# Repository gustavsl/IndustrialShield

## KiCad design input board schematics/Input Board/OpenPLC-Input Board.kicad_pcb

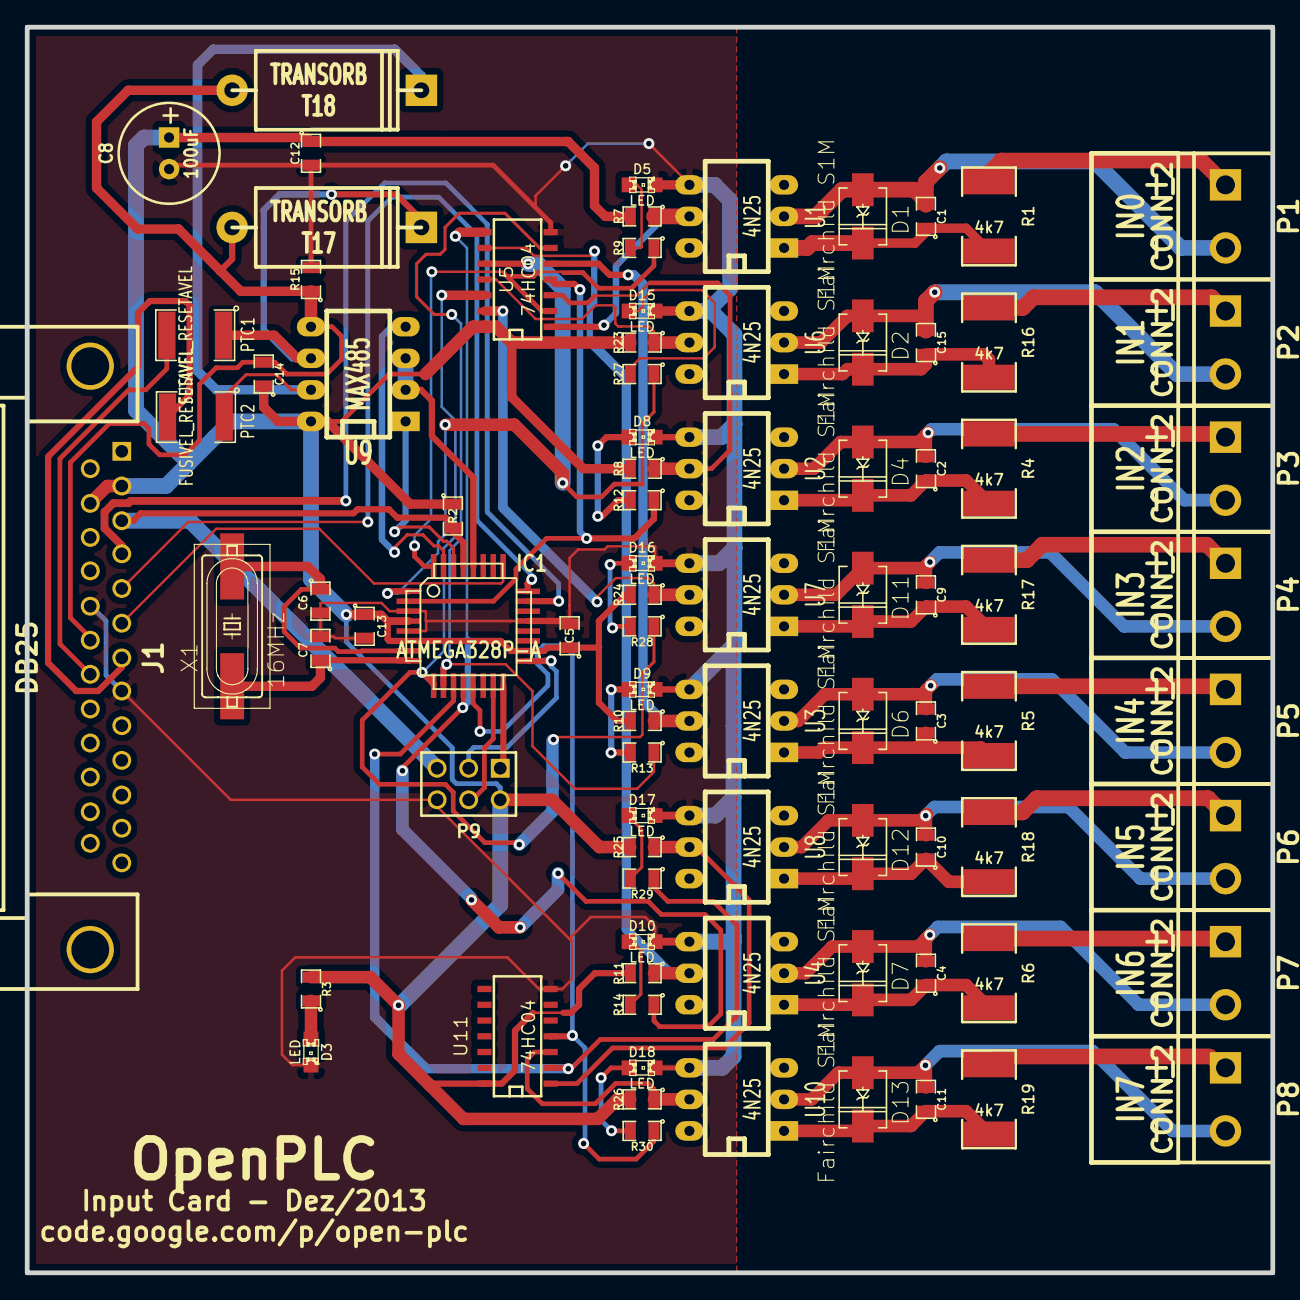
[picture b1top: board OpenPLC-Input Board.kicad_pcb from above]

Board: 2 copper layers, 100.3 x 100.3 mm, 86 parts (0 on the bottom side), 68 nets.

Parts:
C1, C2, C3, C4, C5, C9, C10, C11, C12, C13, C14, C15: 100nF; SM0805
C6, C7: 22pF; SM0805
C8: 100uF; C1V8
D1, D2, D4, D6, D7, D11, D12, D13: Fairchild S1M; DO214_OPLC
D3, D5, D8, D9, D10, D15, D16, D17, D18: LED; LED-0805
IC1: ATMEGA328P-A; TQFP32
J1: DB25; DB25MC
P1, P2, P3, P4, P5, P6, P7, P8: CONN_2; bornier2
P9: ICSP - 3X2; pin_array_3x2
PTC1, PTC2: FUSIVEL_RESETAVEL; SM1812
R1, R4, R5, R6, R16, R17, R18, R19: 4k7; SM2512
R2, R7, R8, R10, R11, R23, R24, R25, R26: 10k; SM0805
R3, R9, R12, R13, R14, R27, R28, R29, R30: 1k; SM0805
R15: 0R; SM0805
T17, T18: TRANSORB; D6
U1, U2, U3, U4, U6, U7, U8, U10: 4N25; DIP-6__300_ELL
U5, U11: 74HC04; SO14E
U9: MAX485; DIP-8__300_ELL
X1: 16MHz; crystal-HC49UP

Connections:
+5V: C5.1, C8.1, C12.1, C13.1, C14.1, IC1.4, IC1.6, IC1.18, J1.2, J1.15, P9.2, R2.1, R3.2, R7.2, R8.2, R10.2, R11.2, R23.2, R24.2, R25.2, R26.2, U5.14, U9.8, U11.14
/A: J1.20, PTC1.2
/B: J1.7, PTC2.2
/CPU_RESET: IC1.29, J1.3, P9.5, R2.2
/D0: IC1.23, J1.4
/D1: IC1.24, J1.5
/D2: IC1.25, J1.6
/E1+: P1.1, R1.1
/E1-: C1.2, D1.1, P1.2, U1.2
/E2+: P2.1, R16.1
/E2-: C15.2, D2.1, P2.2, U6.2
/E3+: P3.1, R4.1
/E3-: C2.2, D4.1, P3.2, U2.2
/E4+: P4.1, R17.1
/E4-: C9.2, D11.1, P4.2, U7.2
/E5+: P5.1, R5.1
/E5-: C3.2, D6.1, P5.2, U3.2
/E6+: P6.1, R18.1
/E6-: C10.2, D12.1, P6.2, U8.2
/E7+: P7.1, R6.1
/E7-: C4.2, D7.1, P7.2, U4.2
/E8+: P8.1, R19.1
/E8-: C11.2, D13.1, P8.2, U10.2
/EN: IC1.28, U9.2, U9.3
/GND_485: C14.2, J1.19, R15.1, T17.1, T18.1, U9.5
/MISO: IC1.16, P9.1
/MOSI: IC1.15, P9.4
/RX: IC1.30, U9.1
/SCK: IC1.17, P9.3
/TX: IC1.31, U9.4
/X0: IC1.32, R9.1, U5.2
/X1: IC1.1, R27.1, U5.10
/X2: IC1.2, R12.1, U5.4
/X3: IC1.9, R28.1, U5.12
/X4: IC1.10, R13.1, U5.6
/X5: IC1.11, R29.1, U11.2
/X6: IC1.12, R14.1, U5.8
/X7: IC1.13, R30.1, U11.4
GND: C5.2, C6.2, C7.2, C8.2, C12.2, C13.2, D3.2, D5.2, D8.2, D9.2, D10.2, D15.2, D16.2, D17.2, D18.2, IC1.3, IC1.5, IC1.21, J1.8, J1.18, P9.6, R15.2, U1.4, U2.4, U3.4, U4.4, U5.7, U6.4, U7.4, U8.4, U10.4, U11.7
unnamed: D3.1, R3.1
unnamed: D17.1, R29.2
unnamed: D9.1, R13.2
unnamed: R10.1, U3.5, U5.5
unnamed: C9.1, D11.2, R17.2, U7.1
unnamed: C2.1, D4.2, R4.2, U2.1
unnamed: C15.1, D2.2, R16.2, U6.1
unnamed: C6.1, IC1.7, X1.2
unnamed: C1.1, D1.2, R1.2, U1.1
unnamed: D5.1, R9.2
unnamed: R23.1, U5.11, U6.5
unnamed: R7.1, U1.5, U5.1
unnamed: C7.1, IC1.8, X1.1
unnamed: D15.1, R27.2
unnamed: PTC2.1, T18.2, U9.7
unnamed: D10.1, R14.2
unnamed: D18.1, R30.2
unnamed: D16.1, R28.2
unnamed: D8.1, R12.2
unnamed: R8.1, U2.5, U5.3
unnamed: R24.1, U5.13, U7.5
unnamed: R26.1, U10.5, U11.3
unnamed: R11.1, U4.5, U5.9
unnamed: R25.1, U8.5, U11.1
unnamed: PTC1.1, T17.2, U9.6
unnamed: C4.1, D7.2, R6.2, U4.1
unnamed: C3.1, D6.2, R5.2, U3.1
unnamed: C11.1, D13.2, R19.2, U10.1
unnamed: C10.1, D12.2, R18.2, U8.1

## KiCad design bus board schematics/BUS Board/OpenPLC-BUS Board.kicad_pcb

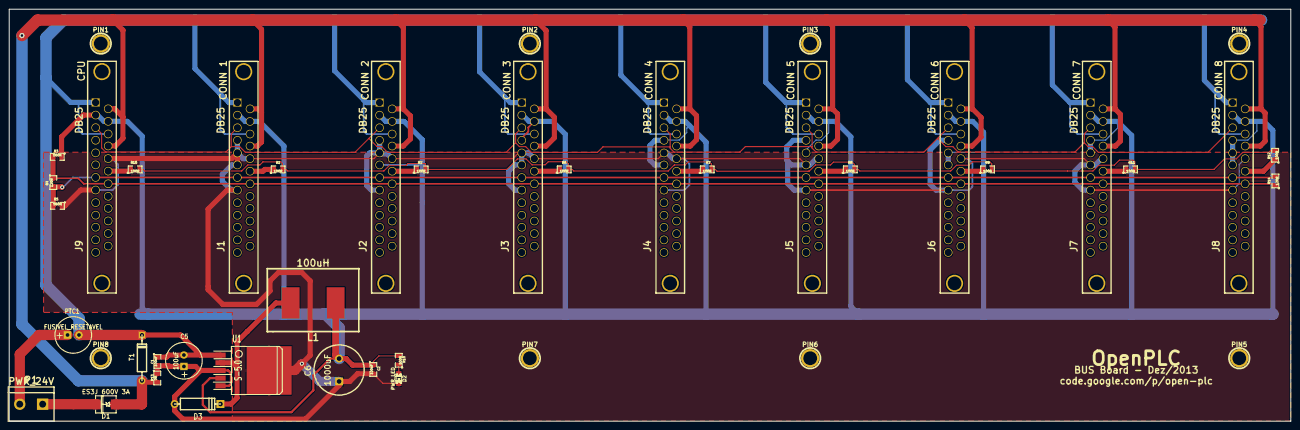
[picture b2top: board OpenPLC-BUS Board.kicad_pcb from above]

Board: 2 copper layers, 284.5 x 91.4 mm, 44 parts (0 on the bottom side), 21 nets.

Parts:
C1, C2: 100nF; SM0805
C5: 100uF; C1V8
C6: 1000uF; C2V10
D1: ES3J 600V 3A; DO-214AA(SMB)
D2: PWR_LED; LED-0805
D3: 1N5822; D4
J1, J2, J3, J4, J5, J6, J7, J8, J9: DB25; DB25_Large
L1: 100uH; bourns-srr1206
P1: PWR_24V; bornier2
PIN1: P1; 1pin
PIN2: P2; 1pin
PIN3: P3; 1pin
PIN4: P4; 1pin
PIN5: P5; 1pin
PIN6: P6; 1pin
PIN7: P7; 1pin
PIN8: P8; 1pin
PTC1: FUSIVEL_RESETAVEL; C1V8
R1, R2, R6, R7, R8, R9, R11, R12, R15: 100R; SM0805
R3, R5: 560R; SM0805
R4, R14: 120R; SM0805
R10: 500R; SM0805
R13: 0R; SM0805
T1: TRANSORB; DO-41
U1: S-5.0; TO263-5

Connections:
+5V: C2.1, C6.2, J1.2, J1.15, J2.2, J2.6, J2.15, J3.2, J3.4, J3.15, J4.2, J4.4, J4.6, J4.15, J5.2, J5.5, J5.15, J6.2, J6.5, J6.6, J6.15, J7.2, J7.4, J7.5, J7.15, J8.2, J8.4, J8.5, J8.6, J8.15, J9.2, J9.15, L1.2, R3.1, R10.2, U1.4
/24V: C1.1, C5.2, J1.1, J1.16, J2.1, J2.16, J3.1, J3.16, J4.1, J4.16, J5.1, J5.16, J6.1, J6.16, J7.1, J7.16, J8.1, J8.16, J9.1, J9.16, PTC1.2, T1.2, U1.1
/485_A: J1.20, J2.20, J3.20, J4.20, J5.20, J6.20, J7.20, J8.20, J9.20, R3.2, R4.1, R14.1
/485_B: J1.7, J2.7, J3.7, J4.7, J5.7, J6.7, J7.7, J8.7, J9.7, R4.2, R5.2, R14.2
/CPU_RESET: J1.3, J2.3, J3.3, J4.3, J5.3, J6.3, J7.3, J8.3, J9.3
/GND_24: D1.1, J1.14, J1.17, J2.14, J2.17, J3.14, J3.17, J4.14, J4.17, J5.14, J5.17, J6.14, J6.17, J7.14, J7.17, J8.14, J8.17, J9.14, J9.17, R13.2, T1.1
/GND_485: R1.2, R2.2, R6.2, R7.2, R8.2, R9.2, R11.2, R12.2, R15.2
GND: C1.2, C2.2, C5.1, C6.1, D2.2, D3.1, J1.4, J1.5, J1.6, J1.8, J1.18, J2.4, J2.5, J2.8, J2.18, J3.5, J3.6, J3.8, J3.18, J4.5, J4.8, J4.18, J5.4, J5.6, J5.8, J5.18, J6.4, J6.8, J6.18, J7.6, J7.8, J7.18, J8.8, J8.18, J9.8, J9.18, R5.1, R13.1, U1.3, U1.5
unnamed: J2.19, R2.1
unnamed: J6.19, R9.1
unnamed: J8.19, R12.1
unnamed: J4.19, R7.1
unnamed: J7.19, R11.1
unnamed: J9.19, R15.1
unnamed: D3.2, L1.1, U1.2
unnamed: P1.2, PTC1.1
unnamed: D1.2, P1.1
unnamed: D2.1, R10.1
unnamed: J5.19, R8.1
unnamed: J1.19, R1.1
unnamed: J3.19, R6.1

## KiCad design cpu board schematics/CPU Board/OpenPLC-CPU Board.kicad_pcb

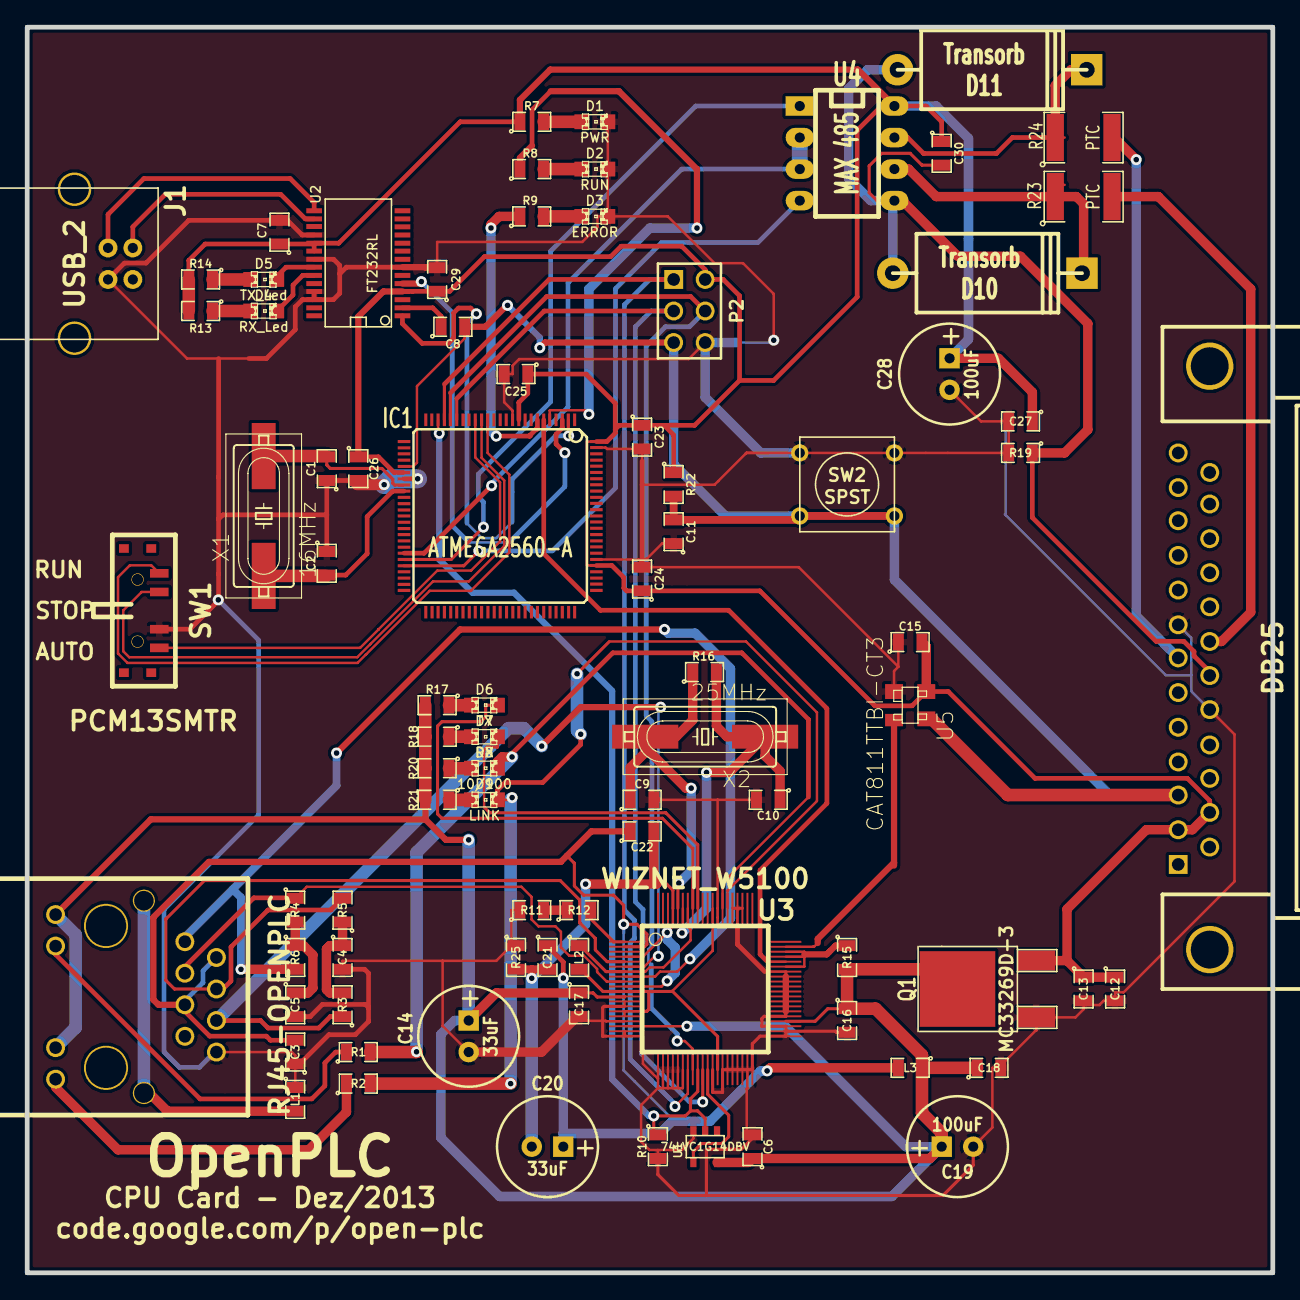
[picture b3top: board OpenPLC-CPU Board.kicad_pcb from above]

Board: 2 copper layers, 100.3 x 100.3 mm, 84 parts (0 on the bottom side), 64 nets.

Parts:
C1, C2, C9, C10: 22pF; SM0805
C3, C4, C5, C6, C7, C8, C11, C12, C15, C16, C17, C18, C21, C22, C23, C24, C25, C26, C27, C29, C30: 100nF; SM0805
C13: 47uF; SM0805
C14, C20: 33uF; C1V8
C19, C28: 100uF; C1V8
D1: PWR; LED-0805
D2: RUN; LED-0805
D3: ERROR; LED-0805
D4: RX_Led; LED-0805
D5: TX_Led; LED-0805
D6: TX; LED-0805
D7: RX; LED-0805
D8: 10/100; LED-0805
D9: LINK; LED-0805
D10, D11: Transorb; D6
IC1: ATMEGA2560-A; TQFP_100
J1: USB_2; USB_B
J2: DB25; DB25MC
L1: BLM21PG300 - 250mA 1uH; SM0805
L2, L3: BLM21PG300; SM0805
P1: RJ45-OPENPLC; RJ45_SI60062
P2: ICSP; pin_array_3x2
Q1: MC33269D-3; DPAK2
R1, R2: 1K; SM0805
R3, R4, R5, R6: 49R9; SM0805
R7, R8, R9, R17, R18, R20, R21: 1k; SM0805
R10, R15, R22: 10k; SM0805
R11: 300R; SM0805
R12: 12k; SM0805
R13, R14: 500R; SM0805
R16: 1M; SM0805
R19, R25: 0R; SM0805
R23, R24: PTC; SM1812
SW1: PCM13SMTR
SW2: SPST; SW_PUSH_SMALL
U1: 74LVC1G14DBV; SOT23-5
U2: FT232RL; SSOP28
U3: WIZNET_W5100; wiznet_w5100
U4: MAX 485; DIP-8__300_ELL
U5: CAT811TTBI-CT3; -SOT143-W
X1: 16MHz; crystal-HC49UP
X2: 25MHz; crystal-HC49UP

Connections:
+3.3V: C6.1, C14.1, C16.1, C17.1, C18.1, C19.1, L3.1, P1.11, P1.13, Q1.2, R15.2, R17.2, R18.2, R20.2, R21.2, U1.5, U3.12, U3.18, U3.44
+5V: C7.1, C12.1, C13.1, C15.2, C23.1, C24.1, C25.1, C26.1, C27.1, C28.1, C29.1, C30.1, IC1.10, IC1.31, IC1.80, IC1.100, J2.2, J2.15, P2.2, Q1.3, R7.1, R13.2, R14.2, R22.1, U2.4, U2.19, U2.20, U4.8, U5.4
/3V3A: C3.2, C20.1, C21.1, C22.1, L3.2, P1.2, P1.5, U3.2
/485_A: J2.20, R23.2
/485_B: J2.7, R24.2
/485_RX: IC1.45, U4.1
/485_TX: IC1.46, U4.4
/CPU_ERROR: IC1.7, R9.1
/CPU_RESET: C8.2, C11.2, IC1.30, J2.3, P2.5, R22.2, SW2.2, U5.3
/CPU_RUN: IC1.5, R8.1
/GND_485: C30.2, D10.1, D11.1, J2.19, R19.1, U4.5
/INT: IC1.6, U3.56
/LINKLED: D9.2, R2.2, U3.66
/MISO: IC1.22, P2.1, U3.27
/MOSI: IC1.21, P2.4, U3.28
/RESET_W: U3.59, U5.2
/RXIN: P1.6, R3.1, U3.6
/RXIP: P1.4, R5.2, U3.5
/SCK: IC1.20, P2.3, U3.30
/SPDLED: D8.2, R1.2, U3.67
/SS: IC1.23, R10.1, U1.2, U3.29
/TXON: P1.3, R4.1, U3.9
/TXOP: P1.1, R6.2, U3.8
/TX_EN: IC1.44, U4.2, U4.3
/USB_RX: IC1.2, U2.1
/USB_TX: IC1.3, U2.5
GND: C1.1, C2.1, C3.1, C4.2, C5.2, C6.2, C7.2, C9.2, C10.2, C11.1, C12.2, C13.2, C14.2, C15.1, C16.2, C17.2, C18.2, C19.2, C23.2, C24.2, C25.2, C26.2, C27.2, C28.2, C29.2, D1.2, D2.2, D3.2, IC1.11, IC1.32, IC1.81, IC1.99, J1.4, J2.8, J2.18, L1.1, P1.8, P2.6, Q1.1, R10.2, R11.1, R19.2, R25.1, SW1.3, SW2.1, U1.3, U2.7, U2.18, U2.21, U2.25, U2.26, U3.13, U3.14, U3.17, U3.19, U3.20, U3.21, U3.22, U3.23, U3.24, U3.25, U3.26, U3.32, U3.34, U3.35, U3.36, U3.37, U3.38, U3.39, U3.40, U3.41, U3.42, U3.43, U3.45, U3.46, U3.47, U3.48, U3.49, U3.50, U3.51, U3.52, U3.53, U3.54, U3.63, U3.64, U3.65, U3.68, U5.1
GNDA: C20.2, C21.2, C22.2, R25.2, U3.4, U3.10, U3.77
unnamed: L2.1, U3.7, U3.74
unnamed: R15.1, U3.55, U3.57, U3.58
unnamed: R12.2, U3.1
unnamed: D6.1, R17.1
unnamed: D7.2, U3.72
unnamed: D7.1, R18.1
unnamed: D6.2, U3.73
unnamed: C10.1, R16.2, U3.75, X2.1
unnamed: D8.1, R20.1
unnamed: D9.1, R21.1
unnamed: R11.2, R12.1
unnamed: C5.1, R4.2, R6.1
unnamed: P1.12, R1.1
unnamed: L1.2, P1.9, P1.10
unnamed: P1.14, R2.1
unnamed: C1.2, IC1.33, X1.2
unnamed: D4.2, U2.23
unnamed: C2.2, IC1.34, X1.1
unnamed: C8.1, U2.2
unnamed: D4.1, R13.1
unnamed: D5.1, R14.1
unnamed: J1.3, U2.15
unnamed: J1.2, U2.16
unnamed: D10.2, R23.1, U4.6
unnamed: D11.2, R24.1, U4.7
unnamed: D2.1, R8.2
unnamed: D3.1, R9.2
unnamed: D1.1, R7.2
unnamed: C9.1, R16.1, U3.76, X2.2
unnamed: L2.2, U3.11, U3.15, U3.16, U3.33, U3.69
unnamed: C4.1, R3.2, R5.1
unnamed: IC1.15, SW1.1
unnamed: IC1.17, SW1.4
unnamed: IC1.16, SW1.2
unnamed: D5.2, U2.22
unnamed: U1.4, U3.31

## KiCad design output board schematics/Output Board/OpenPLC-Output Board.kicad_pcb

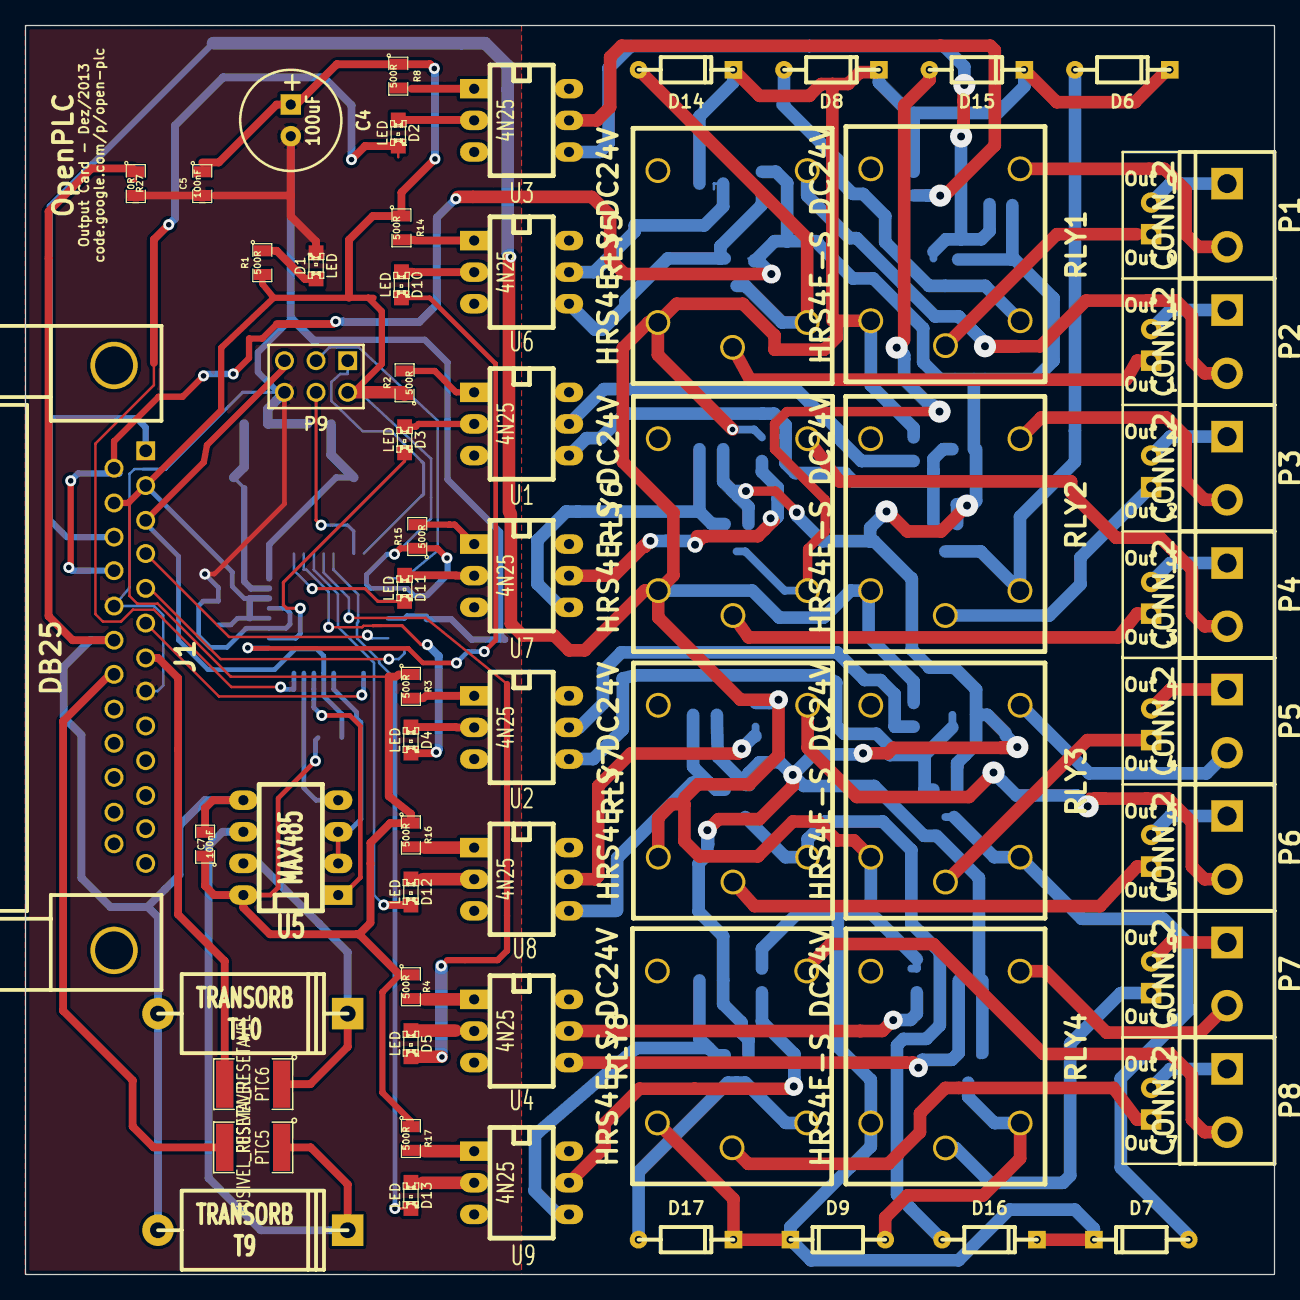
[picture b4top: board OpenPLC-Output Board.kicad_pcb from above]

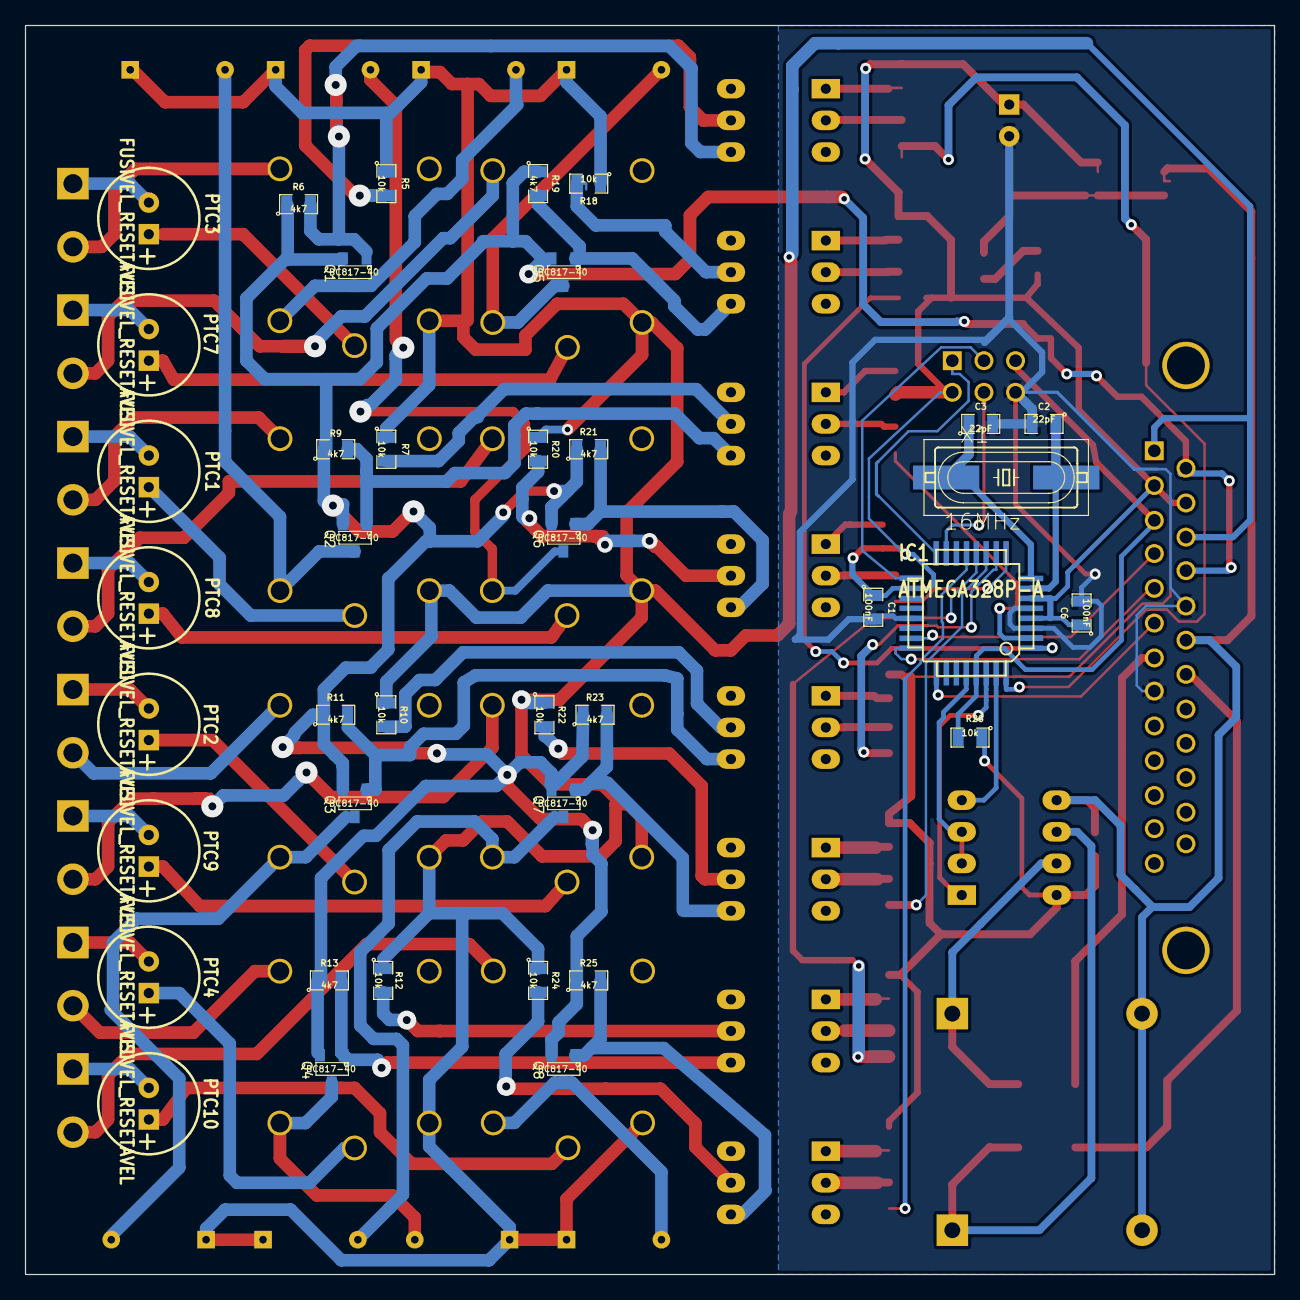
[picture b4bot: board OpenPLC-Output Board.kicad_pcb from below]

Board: 2 copper layers, 100.3 x 100.3 mm, 100 parts (39 on the bottom side), 94 nets.

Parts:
C1, C5, C6, C7: 100nF; SM0805
C2, C3: 22pF; SM0805
C4: 100uF; C1V8
D1, D2, D3, D4, D5, D10, D11, D12, D13: LED; LED-0805
D6, D7, D8, D9, D14, D15, D16, D17: 1N4148; DO-35
IC1: ATMEGA328P-A; TQFP32
J1: DB25; DB25MC
P1, P2, P3, P4, P5, P6, P7, P8: CONN_2; bornier2
P9: ICSP - 3X2; pin_array_3x2
PTC1, PTC2, PTC3, PTC4, PTC7, PTC8, PTC9, PTC10: FUSIVEL_RESETAVEL; C1V8
PTC5, PTC6: FUSIVEL_RESETAVEL; SM1812
Q1, Q2, Q3, Q4, Q5, Q6, Q7, Q8: BC817-40; SOT23
R1, R2, R3, R4, R8, R14, R15, R16, R17: 500R; SM0805
R5, R7, R10, R12, R18, R20, R22, R24, R26: 10k; SM0805
R6, R9, R11, R13, R19, R21, R23, R25: 4k7; SM0805
R27: 0R; SM0805
RLY1, RLY2, RLY3, RLY4, RLY5, RLY6, RLY7, RLY8: HRS4E-S DC24V; Relay_833H-1C-C
T9, T10: TRANSORB; D6
U1, U2, U3, U4, U6, U7, U8, U9: 4N25; DIP-6__300_ELL
U5: MAX485; DIP-8__300_ELL
X1: 16MHz; crystal-HC49UP

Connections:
+5V: C1.1, C4.1, C5.1, C6.1, C7.1, IC1.4, IC1.6, IC1.18, J1.2, J1.15, P9.2, R1.2, R2.1, R3.1, R4.1, R8.1, R14.1, R15.1, R16.1, R17.1, R26.1, U5.8
/24V: D6.2, D7.2, D8.2, D9.2, D14.2, D15.2, D16.2, D17.2, J1.1, J1.16, R5.1, R7.1, R10.1, R12.1, R18.1, R20.1, R22.1, R24.1, RLY1.1, RLY2.1, RLY3.1, RLY4.1, RLY5.1, RLY6.1, RLY7.1, RLY8.1
/A: J1.20, PTC5.2
/B: J1.7, PTC6.2
/CPU_RESET: IC1.29, J1.3, P9.5, R26.2
/D0: IC1.23, J1.4
/D1: IC1.24, J1.5
/D2: IC1.25, J1.6
/EN: IC1.28, U5.2, U5.3
/GND_24: J1.14, J1.17, Q1.2, Q2.2, Q3.2, Q4.2, Q5.2, Q6.2, Q7.2, Q8.2, R6.1, R9.1, R11.1, R13.1, R19.1, R21.1, R23.1, R25.1
/GND_485: C7.2, J1.19, R27.1, T9.1, T10.1, U5.5
/MISO: IC1.16, P9.1
/MOSI: IC1.15, P9.4
/Out1A: P1.1, PTC3.2
/Out1B: P1.2, RLY1.5
/Out2A: P2.1, PTC7.2
/Out2B: P2.2, RLY5.5
/Out3A: P3.1, PTC1.2
/Out3B: P3.2, RLY2.5
/Out4A: P4.1, PTC8.2
/Out4B: P4.2, RLY6.5
/Out5A: P5.1, PTC2.2
/Out5B: P5.2, RLY3.5
/Out6A: P6.1, PTC9.2
/Out6B: P6.2, RLY7.5
/Out7A: P7.1, PTC4.2
/Out7B: P7.2, RLY4.5
/Out8A: P8.1, PTC10.2
/Out8B: P8.2, RLY8.5
/RX: IC1.30, U5.1
/SCK: IC1.17, P9.3
/TX: IC1.31, U5.4
/Y0: D2.2, IC1.32
/Y1: D10.2, IC1.1
/Y2: D3.2, IC1.2
/Y3: D11.2, IC1.9
/Y4: D4.2, IC1.10
/Y5: D12.2, IC1.11
/Y6: D5.2, IC1.12
/Y7: D13.2, IC1.13
GND: C1.2, C2.2, C3.2, C4.2, C5.2, C6.2, D1.2, IC1.3, IC1.5, IC1.21, J1.8, J1.18, P9.6, R27.2
unnamed: Q2.1, R9.2, U1.4
unnamed: R15.2, U7.1
unnamed: D11.1, U7.2
unnamed: R20.2, U7.5
unnamed: R7.2, U1.5
unnamed: R2.2, U1.1
unnamed: D3.1, U1.2
unnamed: D6.1, Q2.3, RLY2.2
unnamed: PTC1.1, RLY2.3
unnamed: R5.2, U3.5
unnamed: D14.1, Q5.3, RLY5.2
unnamed: PTC7.1, RLY5.3
unnamed: Q5.1, R19.2, U6.4
unnamed: PTC8.1, RLY6.3
unnamed: R18.2, U6.5
unnamed: R14.2, U6.1
unnamed: D10.1, U6.2
unnamed: R16.2, U8.1
unnamed: D12.1, U8.2
unnamed: PTC9.1, RLY7.3
unnamed: R22.2, U8.5
unnamed: D7.1, Q3.3, RLY3.2
unnamed: PTC2.1, RLY3.3
unnamed: R24.2, U9.5
unnamed: R4.2, U4.1
unnamed: D5.1, U4.2
unnamed: PTC4.1, RLY4.3
unnamed: PTC10.1, RLY8.3
unnamed: R17.2, U9.1
unnamed: D13.1, U9.2
unnamed: D17.1, Q8.3, RLY8.2
unnamed: Q8.1, R25.2, U9.4
unnamed: R12.2, U4.5
unnamed: R8.2, U3.1
unnamed: PTC6.1, T10.2, U5.7
unnamed: PTC5.1, T9.2, U5.6
unnamed: D1.1, R1.1
unnamed: PTC3.1, RLY1.3
unnamed: D2.1, U3.2
unnamed: C3.1, IC1.8, X1.1
unnamed: C2.1, IC1.7, X1.2
unnamed: D15.1, Q6.3, RLY6.2
unnamed: Q1.1, R6.2, U3.4
unnamed: D8.1, Q1.3, RLY1.2
unnamed: Q6.1, R21.2, U7.4
unnamed: Q3.1, R11.2, U2.4
unnamed: R3.2, U2.1
unnamed: D4.1, U2.2
unnamed: R10.2, U2.5
unnamed: Q4.1, R13.2, U4.4
unnamed: D9.1, Q4.3, RLY4.2
unnamed: Q7.1, R23.2, U8.4
unnamed: D16.1, Q7.3, RLY7.2
